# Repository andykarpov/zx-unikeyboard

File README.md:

# zx-unikeyboard-ps2

This is a ps/2 keyboard controller that allows to connect any keyboard matrix and remap its keys into a ps/2 keyboard.

Based on zx-unikeyboard controller 
https://github.com/valerium-labs/zx-unikeyboard 

Based on ideas of converting a custom keyboard into PS/2-keyboard https://zx-pk.ru/threads/32497-kak-peredelat-prakticheski-lyubuyu-klaviaturu-v-ps-2.html 
and PS/2-CPLD-keyboard controller by andykarpov https://github.com/andykarpov/ps2_cpld_kbd

Unikeyboard ps/2 controller lets you connect any laptop or desktop keyboard matrix (up to 26 pins in any order), 
scan its keypresses to collect the pins interaction (AVR-Keyexplorer module), build an array of its keys and then "learn" 
a controller firmware (avr_kbd_ps2) to convert your keyboard layout into standard ps/2 keyboard.

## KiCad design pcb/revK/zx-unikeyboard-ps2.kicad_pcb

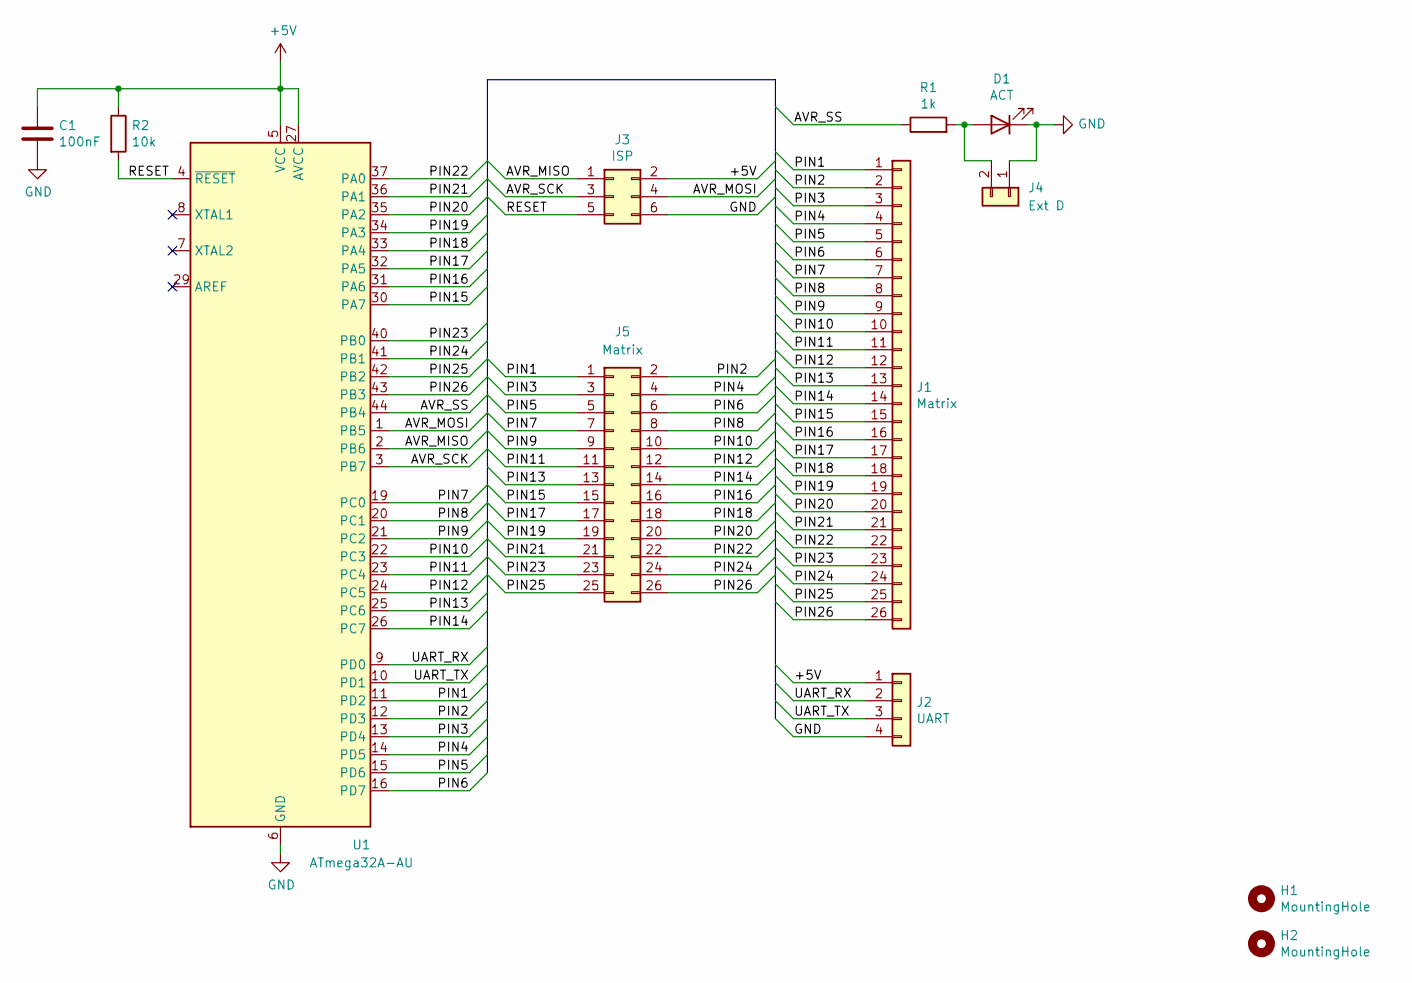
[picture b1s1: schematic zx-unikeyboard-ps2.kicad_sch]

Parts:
C1: 100nF; C_0805_2012Metric_Pad1.18x1.45mm_HandSolder
D1: ACT; LED_0805_2012Metric_Pad1.15x1.40mm_HandSolder
H1, H2: MountingHole; MountingHole_2.1mm
J1: Matrix; TE_2-84952-6_1x26-1MP_P1.0mm_Horizontal
J2: UART; PinHeader_1x04_P2.54mm_Vertical
J3: ISP; PinHeader_2x03_P2.54mm_Vertical
J4: Ext D; PinHeader_1x02_P2.54mm_Vertical
J5: Matrix; PinHeader_2x13_P2.54mm_Vertical
R1: 1k; R_0805_2012Metric_Pad1.20x1.40mm_HandSolder
R2: 10k; R_0805_2012Metric_Pad1.20x1.40mm_HandSolder
U1: ATmega32A-AU; TQFP-44_10x10mm_P0.8mm

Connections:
+5V: C1.1, J2.1, J3.2, R2.1, U1.5 (VCC), U1.17 (VCC), U1.27 (AVCC), U1.38 (VCC)
/AVR_MISO: J3.1, U1.2 (PB6)
/AVR_MOSI: J3.4, U1.1 (PB5)
/AVR_SCK: J3.3, U1.3 (PB7)
/AVR_SS: R1.1, U1.44 (PB4)
/PIN1: J1.1, J5.1, U1.11 (PD2)
/PIN2: J1.2, J5.2, U1.12 (PD3)
/PIN3: J1.3, J5.3, U1.13 (PD4)
/PIN4: J1.4, J5.4, U1.14 (PD5)
/PIN5: J1.5, J5.5, U1.15 (PD6)
/PIN6: J1.6, J5.6, U1.16 (PD7)
/PIN7: J1.7, J5.7, U1.19 (PC0)
/PIN8: J1.8, J5.8, U1.20 (PC1)
/PIN9: J1.9, J5.9, U1.21 (PC2)
/PIN10: J1.10, J5.10, U1.22 (PC3)
/PIN11: J1.11, J5.11, U1.23 (PC4)
/PIN12: J1.12, J5.12, U1.24 (PC5)
/PIN13: J1.13, J5.13, U1.25 (PC6)
/PIN14: J1.14, J5.14, U1.26 (PC7)
/PIN15: J1.15, J5.15, U1.30 (PA7)
/PIN16: J1.16, J5.16, U1.31 (PA6)
/PIN17: J1.17, J5.17, U1.32 (PA5)
/PIN18: J1.18, J5.18, U1.33 (PA4)
/PIN19: J1.19, J5.19, U1.34 (PA3)
/PIN20: J1.20, J5.20, U1.35 (PA2)
/PIN21: J1.21, J5.21, U1.36 (PA1)
/PIN22: J1.22, J5.22, U1.37 (PA0)
/PIN23: J1.23, J5.23, U1.40 (PB0)
/PIN24: J1.24, J5.24, U1.41 (PB1)
/PIN25: J1.25, J5.25, U1.42 (PB2)
/PIN26: J1.26, J5.26, U1.43 (PB3)
/RESET: J3.5, R2.2, U1.4 (~RESET)
/UART_RX: J2.2, U1.9 (PD0)
/UART_TX: J2.3, U1.10 (PD1)
GND: C1.2, D1.1 (K), J2.4, J3.6, J4.1, U1.6 (GND), U1.18 (GND), U1.28 (GND), U1.39 (GND)
unnamed: D1.2 (A), J4.2, R1.2

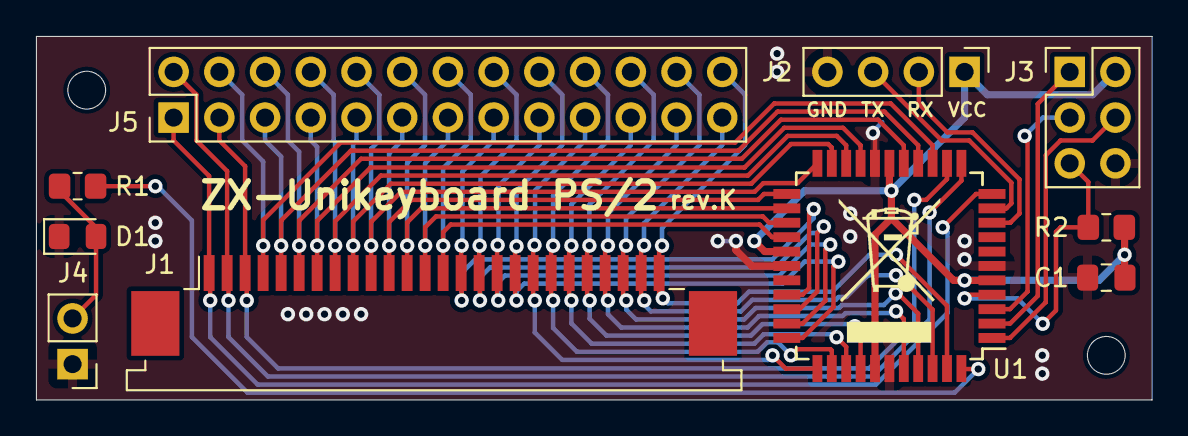
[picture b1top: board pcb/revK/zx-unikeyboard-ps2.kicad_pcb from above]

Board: 2 copper layers, 62.0 x 20.2 mm, 12 parts (0 on the bottom side), 36 nets.

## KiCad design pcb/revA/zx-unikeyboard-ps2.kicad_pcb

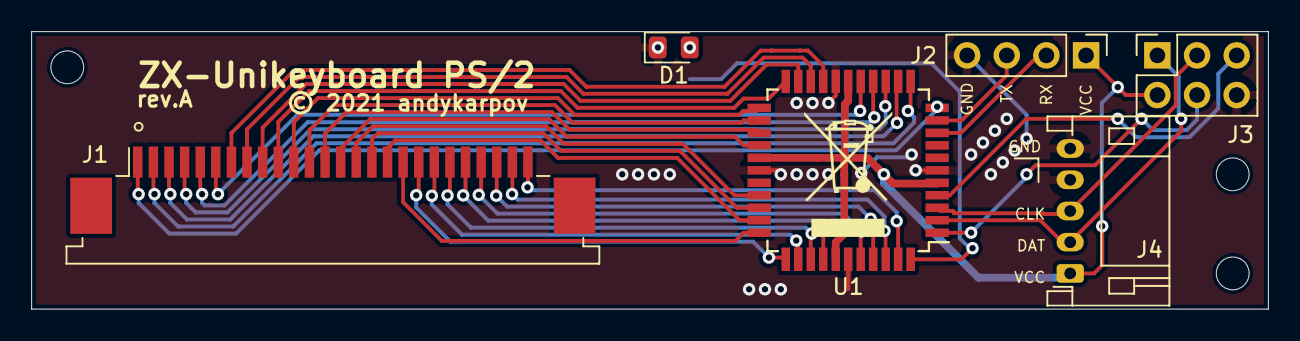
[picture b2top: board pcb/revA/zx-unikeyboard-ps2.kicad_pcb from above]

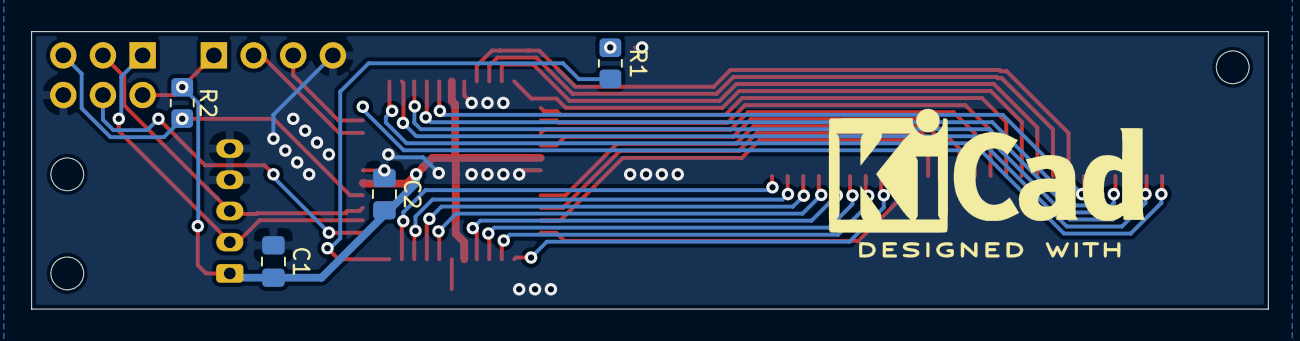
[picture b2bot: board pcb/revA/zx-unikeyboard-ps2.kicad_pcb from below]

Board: 2 copper layers, 79.2 x 17.8 mm, 13 parts (4 on the bottom side), 36 nets.

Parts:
C1, C2: 100nF; C_0805_2012Metric_Pad1.18x1.45mm_HandSolder
D1: ACT; LED_0805_2012Metric_Pad1.15x1.40mm_HandSolder
H1, H2, H3: MountingHole; MountingHole_2.1mm
J1: MATRIX; TE_2-84952-6_1x26-1MP_P1.0mm_Horizontal
J2: UART; PinHeader_1x04_P2.54mm_Vertical
J3: ISP; PinSocket_2x03_P2.54mm_Vertical
J4: PS/2; JST_PH_S5B-PH-K_1x05_P2.00mm_Horizontal
R1: 1k; R_0805_2012Metric_Pad1.20x1.40mm_HandSolder
R2: 10k; R_0805_2012Metric_Pad1.20x1.40mm_HandSolder
U1: ATmega32A-AU; TQFP-44_10x10mm_P0.8mm

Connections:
+5V: C1.1, C2.1, J2.1, J3.2, J4.1, R2.1, U1.5, U1.17, U1.27, U1.38
/AVR_MISO: J3.1, J4.2, U1.2
/AVR_MOSI: J3.4, U1.1
/AVR_SCK: J3.3, J4.3, U1.3
/AVR_SS: R1.1, U1.44
/PIN1: J1.1, U1.11
/PIN2: J1.2, U1.12
/PIN3: J1.3, U1.13
/PIN4: J1.4, U1.14
/PIN5: J1.5, U1.15
/PIN6: J1.6, U1.16
/PIN7: J1.7, U1.19
/PIN8: J1.8, U1.20
/PIN9: J1.9, U1.21
/PIN10: J1.10, U1.22
/PIN11: J1.11, U1.23
/PIN12: J1.12, U1.24
/PIN13: J1.13, U1.25
/PIN14: J1.14, U1.26
/PIN15: J1.15, U1.30
/PIN16: J1.16, U1.31
/PIN17: J1.17, U1.32
/PIN18: J1.18, U1.33
/PIN19: J1.19, U1.34
/PIN20: J1.20, U1.35
/PIN21: J1.21, U1.36
/PIN22: J1.22, U1.37
/PIN23: J1.23, U1.40
/PIN24: J1.24, U1.41
/PIN25: J1.25, U1.42
/PIN26: J1.26, U1.43
/RESET: J3.5, R2.2, U1.4
/UART_RX: J2.2, U1.9
/UART_TX: J2.3, U1.10
GND: C1.2, C2.2, D1.1, J2.4, J3.6, J4.4, J4.5, U1.6, U1.18, U1.28, U1.39
unnamed: D1.2, R1.2

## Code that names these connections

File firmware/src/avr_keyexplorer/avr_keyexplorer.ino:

/*
 * This is and AVR firmware source code for "Unikeyboard explorer" (keyboard matrix scanning software).
 * Scans any keyboard of up to 26 pins and generates the debug output on UART for col/row of key pressed.
 * 
 * Based on AVR keyboard firmware for ps2_cpld_kbd project
 * @author Andy Karpov <andy.karpov@gmail.com>
 * Ukraine, 2019
 * 
 * Ported to ATMega32 and redesigned for custom keyboard matrix by Valeriy Matveyev
 * valerium@rambler.ru
 * Russia, 2021
 * 
 */

#define PINS_MAX 27

#define PIN1 PIN_PD2
#define PIN2 PIN_PD3
#define PIN3 PIN_PD4
#define PIN4 PIN_PD5
#define PIN5 PIN_PD6
#define PIN6 PIN_PD7
#define PIN7 PIN_PC0
#define PIN8 PIN_PC1
#define PIN9 PIN_PC2
#define PIN10 PIN_PC3
#define PIN11 PIN_PC4
#define PIN12 PIN_PC5
#define PIN13 PIN_PC6
#define PIN14 PIN_PC7
#define PIN15 PIN_PA7
#define PIN16 PIN_PA6
#define PIN17 PIN_PA5
#define PIN18 PIN_PA4
#define PIN19 PIN_PA3
#define PIN20 PIN_PA2
#define PIN21 PIN_PA1
#define PIN22 PIN_PA0
#define PIN23 PIN_PB0
#define PIN24 PIN_PB1
#define PIN25 PIN_PB2
#define PIN26 PIN_PB3
#define PIN27 PIN_PB4

const uint8_t pins[PINS_MAX] = 
{
  PIN1, PIN2, PIN3, PIN4, PIN5, PIN6, PIN7, PIN8, PIN9, PIN10, 
  PIN11, PIN12, PIN13, PIN14, PIN15, PIN16, PIN17, PIN18, PIN19, PIN20,
  PIN21, PIN22, PIN23, PIN24, PIN25, PIN26, PIN27
};


// initial setup
void setup()
{
  for (uint8_t i=0; i<PINS_MAX; i++) pinMode (pins[i], INPUT_PULLUP);

  Serial.begin(115200);
  Serial.flush();
  Serial.println(F("Unikeyboard matrix explorer v1.0"));
}

// main loop
void loop()
{
  uint8_t colcount, rowcount;

  for (colcount=0; colcount<PINS_MAX; colcount++)
   {
     for (rowcount=0; rowcount<PINS_MAX; rowcount++) pinMode (pins[rowcount], INPUT_PULLUP);
     
     pinMode (pins[colcount], OUTPUT);
     digitalWrite (pins[colcount], LOW);
     
     for (rowcount=0; rowcount<PINS_MAX; rowcount++)
              if ( (rowcount != colcount) and !digitalRead(pins[rowcount]) )
                  {
                  Serial.println ("Pressed key ("+String((colcount<rowcount?colcount:rowcount)+1)+", "+String((colcount<rowcount?rowcount:colcount)+1)+")");
                  delay (300);
                  }
   }
}

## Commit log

2021-05-01 Added PS/2 version
2021-05-01 Added rendered photo
2021-05-01 Fixed master->main
2021-05-01 Small improvements to PCB rev.A
2021-05-01 Updated howto
2021-07-16 Samsung X360 keyboard support
2021-09-02 Added code for Sven Infra7000
2021-09-02 Added template for SVEN Infra 7000
2021-09-02 Added binary for sven infra 7000
2021-09-03 Fixed keyboard scan (except Enter)
2021-09-03 new reading ;)
2021-09-03 new build
2021-09-25 Fixed ESC, added INS key emulation on Fn+Del
2021-09-25 Added more Fn hotkeys (scroll lock, pause, ptrscr, etc)
2021-11-24 initial commit for art5263 keyboard
2021-11-25 fixed scan
2021-11-25 fixed build script
2021-11-25 Release
2021-11-25 Fixed ESC
2021-11-25 New release
2021-11-25 fixed KEY_ESC index
2021-12-20 Updated release with fixed ESC and other improvements
2022-01-04 Added eeepc900 keyboard support
2022-01-04 Binaries for eeepc900 kbd
2022-01-05 Hotfix ESC, pause/break
2022-07-05 Added 27pin setup
2022-07-05 Added keyexplorer binary for 27pin header
2022-07-12 Added logic for 27pin notebook matrix
2022-07-12 Build for 27pin keyboard
2022-07-12 hotfixes
2022-07-12 Build
2022-07-12 pin27 mapped to pin3
2022-07-12 turn off debug
2022-07-23 Swap some keys
2022-09-07 Added ASUS ZG5 kbd
2022-09-07 updated release
2022-09-08 fixed FN special keys
2022-09-08 Added debug mode
2022-10-15 Updated library with scancodeset support
2024-01-26 revK
2024-01-26 Updated PCB

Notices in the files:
pcb/revA/zx-unikeyboard-ps2.kicad_pcb:
© 2021 andykarpov
pcb/revK/zx-unikeyboard-ps2.kicad_pcb:
© 2024
